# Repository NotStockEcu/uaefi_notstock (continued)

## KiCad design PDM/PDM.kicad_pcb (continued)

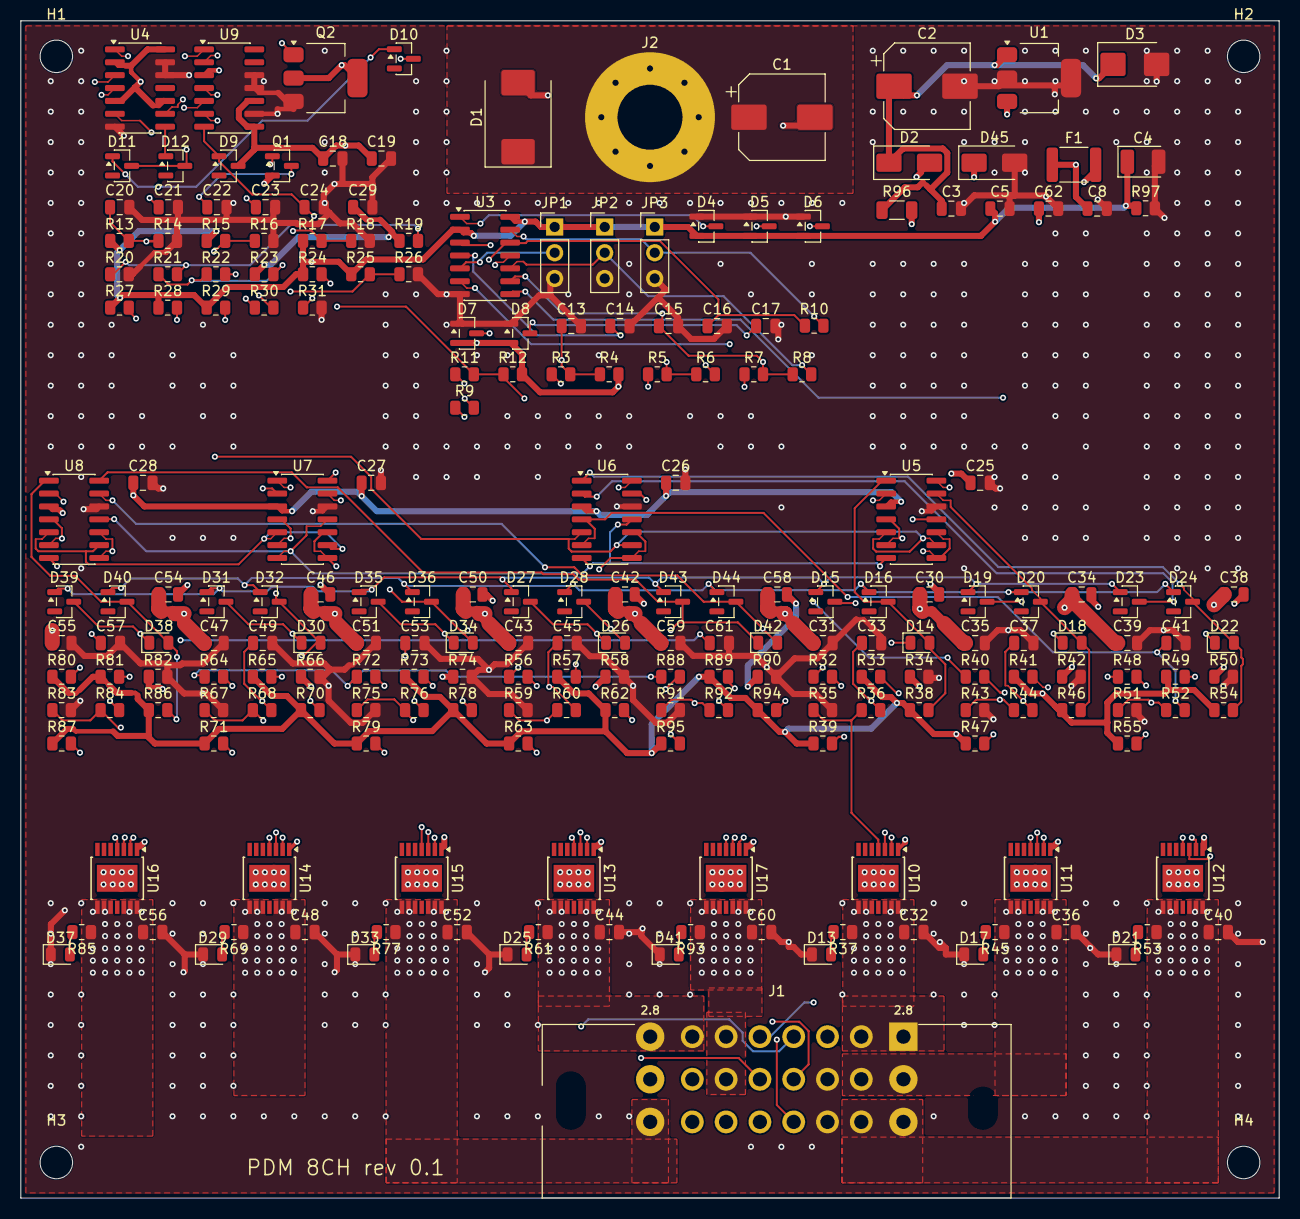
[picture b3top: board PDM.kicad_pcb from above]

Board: 4 copper layers, 124.0 x 116.0 mm, 224 parts (0 on the bottom side), 113 nets.

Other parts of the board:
H1, H2, H3, H4: M3; MountingHole_3.2mm_M3

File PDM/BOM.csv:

Qty,Value,Footprint,DNP,References,Manufacturer,MPN
26,10k,Resistor_SMD:R_0805_2012Metric,,R3 R5 R7 R9 R11 R25 R26 R27 R28 R29 R36 R39 R44 R47 R52 R55 R60 R63 R68 R71 R76 R79 R84 R87 R92 R95,Yageo,RC0805FR-0710KL
20,BAT54,Package_TO_SOT_SMD:SOT-23,,D9 D10 D11 D12 D15 D16 D19 D20 D23 D24 D27 D28 D31 D32 D35 D36 D39 D40 D43 D44,Nexperia,"BAT54,215"
17,4k7,Resistor_SMD:R_0805_2012Metric,,R30 R32 R33 R40 R41 R48 R49 R56 R57 R64 R65 R72 R73 R80 R81 R88 R89,Yageo,RC0805FR-074K7L
14,100n/50V,Capacitor_SMD:C_0805_2012Metric,,C3 C25 C26 C27 C28 C29 C31 C35 C39 C43 C47 C51 C55 C59,Samsung,CL21B104KBCNNNC
9,1k,Resistor_SMD:R_0805_2012Metric,,R38 R46 R54 R62 R70 R78 R86 R94 R97,Yageo,RC0805FR-071KL
8,10n/50V,Capacitor_SMD:C_0805_2012Metric,,C32 C36 C40 C44 C48 C52 C56 C60,Samsung,CL21B103KBANNNC
8,10u/16V,Capacitor_SMD:C_0805_2012Metric,,C33 C37 C41 C45 C49 C53 C57 C61,Samsung,CL21A106KOQNNNE
8,1k 1%,Resistor_SMD:R_0805_2012Metric,,R35 R43 R51 R59 R67 R75 R83 R91,Yageo,RC0805FR-071KL
8,3k9,Resistor_SMD:R_0805_2012Metric,,R37 R45 R53 R61 R69 R77 R85 R93,Yageo,RC0805FR-073K9L
8,47R,Resistor_SMD:R_0805_2012Metric,,R34 R42 R50 R58 R66 R74 R82 R90,Yageo,RC0805FR-0747RL
8,47n DNP,Capacitor_SMD:C_0805_2012Metric,DNP,C30 C34 C38 C42 C46 C50 C54 C58,Samsung,CL21B473KBANNNC
8,BTS7002-1EPP,Package_SO:Infineon_PG-TSDSO-14-22,,U10 U11 U12 U13 U14 U15 U16 U17,Infineon,BTS70021EPPXUMA1
8,GREEN,LED_SMD:LED_0805_2012Metric,,D13 D17 D21 D25 D29 D33 D37 D41,Wurth Elektronik,150080GS75000
8,RED,LED_SMD:LED_0805_2012Metric,,D14 D18 D22 D26 D30 D34 D38 D42,Wurth Elektronik,150080RS75000
6,10n,Capacitor_SMD:C_0805_2012Metric,,C13 C14 C15 C16 C17 C22,Samsung,CL21B103KBANNNC
5,100n,Capacitor_SMD:C_0805_2012Metric,,C5 C18 C19 C20 C21,Samsung,CL21B104KBCNNNC
5,47k,Resistor_SMD:R_0805_2012Metric,,R4 R6 R8 R10 R12,Yageo,RC0805FR-0747KL
5,BAV99,Package_TO_SOT_SMD:SOT-23,,D4 D5 D6 D7 D8,Nexperia,"BAV99,215"
5,LM2901AVQDR (-Q1),Package_SO:SOIC-14_3.9x8.7mm_P1.27mm,,U5 U6 U7 U8 U9,Texas Instruments,LM2901AVQDRQ1
4,100k,Resistor_SMD:R_0805_2012Metric,,R19 R20 R21 R31,Yageo,RC0805FR-07100KL
3,LS/+12V,Connector_PinHeader_2.54mm:PinHeader_1x03_P2.54mm_Vertical,,JP1 JP2 JP3,Wurth Elektronik,61300311121
2,10k 1%,Resistor_SMD:R_0805_2012Metric,,R14 R16,Yageo,RC0805FR-0710KL
2,47u/50V,Capacitor_SMD:CP_Elec_8x10,,C1 C2,Panasonic,EEE-FK1H470P
2,74HC86-Q100,Package_SO:SOIC-14_3.9x8.7mm_P1.27mm,,U3 U4,Nexperia,74HC86D-Q100J
1,0.5A PTC 1812L050/33,Fuse:Fuse_1812_4532Metric,,F1,Littelfuse,1812L050/33MR
1,100k 1%,Resistor_SMD:R_0805_2012Metric,,R18,Yageo,RC0805FR-07100KL
1,10u,Capacitor_SMD:C_0805_2012Metric,,C24,Samsung,CL21A106KOQNNNE
1,18V 1W SMAZ18,Diode_SMD:D_SMA,,D45,Diodes Inc.,SMAZ18-13-F
1,1M,Resistor_SMD:R_0805_2012Metric,,R22,Yageo,RC0805FR-071ML
1,1u/50V,Capacitor_SMD:C_0805_2012Metric,,C62,Samsung,CL21B105KBFNNNE
1,220n/100V,Capacitor_SMD:C_0805_2012Metric,,C8,Murata,GCM21BR72A224KA37L
1,22k,Resistor_SMD:R_0805_2012Metric,,R23,Yageo,RC0805FR-0722KL
1,22u/10V tant,Capacitor_Tantalum_SMD:CP_EIA-3528-21_Kemet-B,,C4,KEMET,T491B226K010AT
1,300k,Resistor_SMD:R_0805_2012Metric,,R24,Yageo,RC0805FR-07300KL
1,330n,Capacitor_SMD:C_0805_2012Metric,,C23,Samsung,CL21B334KBFNNNE
1,35k7 1%,Resistor_SMD:R_0805_2012Metric,,R13,Yageo,RC0805FR-0735K7L
1,470R,Resistor_SMD:R_1206_3216Metric,,R96,Yageo,RC1206FR-07470RL
1,66k5 1%,Resistor_SMD:R_0805_2012Metric,,R15,Yageo,RC0805FR-0766K5L
1,68k1 1%,Resistor_SMD:R_0805_2012Metric,,R17,Yageo,RC0805FR-0768K1L
1,BSP75N,Package_TO_SOT_SMD:SOT-223-3_TabPin2,,Q2,Infineon,BSP75NH6327XTSA1
1,BSS84,Package_TO_SOT_SMD:SOT-23,,Q1,Nexperia,"BSS84,215"
1,HCCPHPE24BKA90F,PDM:Aptiv_SICMA_HCCPHPE24BKA90F_24P_RA,,J1,Amphenol FCI,HCCPHPE24BKA90F
1,LM2937IMP-5.0,Package_TO_SOT_SMD:SOT-223-3_TabPin2,,U1,Texas Instruments,LM2937IMP-5.0/NOPB
1,M6 VBAT,MountingHole:MountingHole_6.4mm_M6_Pad_Via,,J2,-,-
1,SMBJ33A,Diode_SMD:D_SMB,,D3,Littelfuse,SMBJ33A
1,SMCJ33A,Diode_SMD:D_SMC,,D1,Littelfuse,SMCJ33A
1,SS34,Diode_SMD:D_SMA,,D2,Vishay,SS34-E3/61T

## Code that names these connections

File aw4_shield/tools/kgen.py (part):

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defbox('PC817','U',[("1","A"),("2","K")],[("4","C"),("3","E")])
defbox('RELAY_SPDT','K',[("2","COIL1"),("5","COIL2")],[("1","COM"),("4","NC"),("3","NO")])
defbox('REG_5V','U',[("1","VIN"),("2","GND")],[("3","VOUT")])
defbox('MOD_P1','J',[("1","GPIO7 UP"),("2","GPIO9 DOWN"),("3","GPIO8 READY"),("4","GPIO22 LOCKUP"),("5","GPIO21 RELE"),("6","GPIO18 (LCD)"),("7","GPIO23 SOL1"),("8","GPIO11 SOL2"),("9","GPIO6 SOL3"),("10","GPIO5"),("11","GPIO20 (LCD)"),("12","GPIO19 (LCD)"),("13","GND"),("14","5V")],[])
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defbox('LM393','U',[("3","+INA"),("2","-INA"),("5","+INB"),("6","-INB")],[("8","VCC"),("4","GND"),("1","OUTA"),("7","OUTB")])
defbox('CONN3','J',[("1","1"),("2","2"),("3","3")],[])
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SOCK="Connector_PinSocket_2.54mm:PinSocket_1x14_P2.54mm_Vertical"
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add('MOD_P2',"P2 modulu RP2350-Touch-LCD-2",SOCK,120,140,{"1":"+3V3_MOD","2":"GND","3":"BRAKE_D","7":"SOL1_SNS","8":"CAN_TX","9":"SOL2_SNS","10":"CAN_RX","11":"SOL3_SNS","12":"VSS_OUT","13":"GND"},"J",note="dutinková lišta 1x14 pro lištu P2 modulu",ref="J8",hand=True,mpn="Sullins PPTC141LFBN-RC")
add('CONN3',"J6 rezerva GPIO5 / 3V3 / GND","Connector_PinHeader_2.54mm:PinHeader_1x03_P2.54mm_Vertical",165,140,{"1":"GPIO5_SPARE","2":"+3V3_MOD","3":"GND"},"J",ref="J6",hand=True,mpn="kolíková lišta 1x3 2,54 mm")
add('CONN6',"J2 SOL1-3 / TCU1-3",PT(6),195,140,{"1":"SOL1_OUT","2":"SOL2_OUT","3":"SOL3_OUT","4":"TCU1","5":"TCU2","6":"TCU3"},"J",note="1-3 k převodovce, 4-6 z původní TCU",ref="J2",hand=True,mpn="Phoenix PT 1,5/6-3,5-H (1984659)")
add('CONN6',"J3 UP DOWN READY LOCKUP",PT(6),255,140,{"1":"+5V","2":"GND","3":"UP_IN","4":"DOWN_IN","5":"READY_IN","6":"LOCKUP_IN"},"J",ref="J3",hand=True,mpn="Phoenix PT 1,5/6-3,5-H (1984659)")

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    x+=96

# --- Relay coil drive ---
text(20,232,"CÍVKY RELÉ K1-K3 (společné): READY přepínač AND GPIO21 (aktivní HIGH přes Q6)",3)
res("330",40,258,"READY_IN","RLY_A",ref="R13")
opto(75,258,"RLY_A","RLY_K","RLY_C","Q4_B",ref="U3")
res("2k2",110,258,"+12V_AUX","RLY_C",ref="R14")
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diode("1N4148W",190,258,"+12V_AUX","K_LOW",note="flyback cívek",ref="D9")
res("2k2",210,258,"+12V_AUX","LED_A",ref="R16")
add('LED',"zelená READY","LED_SMD:LED_0805_2012Metric",230,258,{"1":"K_LOW","2":"LED_A"},"D",ref="D10",lcsc="C2297",mpn="KT-0805G")
npn(280,258,"Q6_B","RLY_K","GND",note="spíná LED optočlenu U3 z GPIO21 (3,3 V)",ref="Q6")
res("4k7",255,258,"K_CTRL","Q6_B",ref="R26")
res("47k",305,258,"Q6_B","GND",note="bez modulu drží Q6 zavřený (relé odpadlá)",ref="R27")

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    res("22k",xb+70,yy,"+12V_AUX",f"G{n}",note="gate pull-up (22k: optočlen stačí ~0,5 mA i z 3,3 V GPIO)",ref=f"R{rb+2}")
    diode("MMSZ5245B",xb+88,yy,"+12V_AUX",f"G{n}",note="zener 15 V gate-source",ref=f"D{9+2*n}")
    pfet(xb+118,yy+25,f"G{n}",f"SOL{n}_NO","+12V_SW",ref=f"Q{2+n}")
    add('RELAY_SPDT',"G5LE-1 12V SPDT","Relay_THT:Relay_SPDT_Omron-G5LE-1",xb+158,yy+25,{"2":"+12V_AUX","5":"K_LOW","1":f"SOL{n}_OUT","4":f"TCU{n}","3":f"SOL{n}_NO"},"K",note="čísla pinů relé ověřit podle footprintu",ref=f"K{n}",hand=True,mpn="Omron G5LE-1 DC12")
    diode("M7",xb+158,yy+60,f"SOL{n}_OUT","PGND",note="flyback na straně solenoidu",ref=f"D{10+2*n}")

# --- CAN (rusEFI) ---
text(20,392,"CAN (rusEFI): SN65HVD230 (3,3 V z modulu), TX/RX = GPIO1/GPIO0 (P2), RS na GND = plná rychlost; zakončení 120R přes JP2",3)
add('SN65HVD230',"SN65HVD230DR","Package_SO:SOIC-8_3.9x4.9mm_P1.27mm",60,415,{"1":"CAN_TX","4":"CAN_RX","8":"GND","3":"+3V3_MOD","2":"GND","7":"CANH","6":"CANL"},"U",note="CAN budič 3,3 V; VREF (5) nezapojeno",ref="U7",lcsc="C12084",mpn="SN65HVD230DR")
cap("100nF",110,415,"+3V3_MOD","GND",ref="C9")
res("120",160,415,"CANH","CAN_TERM",note="zakončení sběrnice (osadit JP2, jen když je deska na konci sběrnice)",ref="R28")
add('CONN2',"JP2 zakončení CAN 120R","Connector_PinHeader_2.54mm:PinHeader_1x02_P2.54mm_Vertical",190,415,{"1":"CAN_TERM","2":"CANL"},"J",ref="JP2",hand=True,mpn="kolíková lišta 1x2 + jumper")
add('CONN2',"J4 CAN-H / CAN-L",PT(2),230,415,{"1":"CANH","2":"CANL"},"J",ref="J4",hand=True,mpn="Phoenix PT 1,5/2-3,5-H (1984617)")

# --- Čtení solenoidů, brzda, rychlost (VSS) ---
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for n in (1,2,3): sense(f"SOL{n}_OUT", f"SOL{n}_SNS", 40+(n-1)*96, 30+2*(n-1), 10+(n-1), 16+n)
sense("BRAKE_IN","BRAKE_D",328,36,13,20)
add('CONN2',"J5 BRZDA / VSS",PT(2),430,495,{"1":"BRAKE_IN","2":"VSS_IN"},"J",note="1 = brzdový spínač (+12 V při brzdění), 2 = signál rychlosti (Hall 5/12 V nebo indukční)",ref="J5",hand=True,mpn="Phoenix PT 1,5/2-3,5-H (1984617)")
text(20,530,"RYCHLOST (VSS): komparátor LM393, práh ~0,6 V s hysterezí – Hall 5/12 V i indukční čidlo; výstup otevřený kolektor -> 3V3 -> GPIO10",3)
res("10k",40,560,"VSS_IN","VSS_C",ref="R38")
add('D',"1N5819WS",DI["1N5819WS"][0],62,560,{"1":"VSS_C","2":"GND"},"D",note="záporné napětí z indukčního čidla omezí na ~-0,3 V",ref="D21",lcsc=DI["1N5819WS"][1],mpn="1N5819WS")
add('D',"1N4148WS",DI["1N4148WS"][0],84,560,{"1":"+5V","2":"VSS_C"},"D",note="kladné napětí omezí na 5,7 V",ref="D22",lcsc=DI["1N4148WS"][1],mpn="1N4148WS")
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
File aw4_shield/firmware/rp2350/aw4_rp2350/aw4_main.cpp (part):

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//   (simulátor navíc: t = stupeň, který drží původní TCU, b = brzda, v = auto jede / stojí)
//
// Piny na liště P1 modulu (deska v0.4/v0.5):
//   UP=GPIO7 (P1-1), DOWN=GPIO9 (P1-2), READY=GPIO8 (P1-3), LOCKUP=GPIO22 (P1-4)
//   RELÉ=GPIO21 (P1-5, aktivní HIGH), SOL1=GPIO23 (P1-7), SOL2=GPIO11 (P1-8), SOL3=GPIO6 (P1-9)
// Lišta P2 (deska v0.5):
//   čtení napětí na vodičích solenoidů SOL1/2/3 = GPIO2/3/4 (P2-7/9/11), BRZDA = GPIO28 (P2-3), VSS = GPIO10 (P2-12)
//   Při READY vyp. čtení solenoidů ukazuje, co spíná původní TCU; při READY zap. kontroluje naše výstupy.

#include <Arduino.h>
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
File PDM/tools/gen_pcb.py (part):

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PEGL = (X1 - 32.775, Hc + 6.3, 2.2, 5.0)          # NPTH pegs (x, y, w, h)
PEGR = (X1 + 7.825, Hc + 7.05, 2.2, 3.5)

chre = re.compile(r'^/(OUT|PGND|IS|DEN|PIN|LG|FLT|OVL)(\d)(_F|_N)?$')
# per channel: OUT EMC cap C32+4k, LED resistor R37+8k and green LED D13+4k go onto the edge of the output copper
edge = {ch: (f'C{32 + 4 * (ch - 1)}', f'R{37 + 8 * (ch - 1)}', f'D{13 + 4 * (ch - 1)}') for ch in range(1, 9)}
edge_parts = {r for v in edge.values() for r in v}
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    '/OUT3': (ALL, [(bx[3] - 3.5, TOP, bx[3] + 3.5, H - 1.5), (col[2] - 1.9, C + rb + .1, bx[3] + 3.5, H - 1.5),
                    (col[2] - 1.9, B + 2.0, col[1] + 1.9, H - 1.5)]),
}
# OUT5 / OUT7 run on B.Cu + In2; the BTS OUT pins are on F.Cu, so they also get F.Cu down to the connector area
extra_f = {'/OUT7': (bx[7] - 3.5, TOP, bx[7] + 3.5, C + rb), '/OUT5': (bx[5] - 3.5, TOP, bx[5] + 3.5, B + 1.6)}
# via arrays right below each BTS tie all copper layers of the output together (otherwise only F.Cu carries current there)
for ch, x in bx.items():
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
